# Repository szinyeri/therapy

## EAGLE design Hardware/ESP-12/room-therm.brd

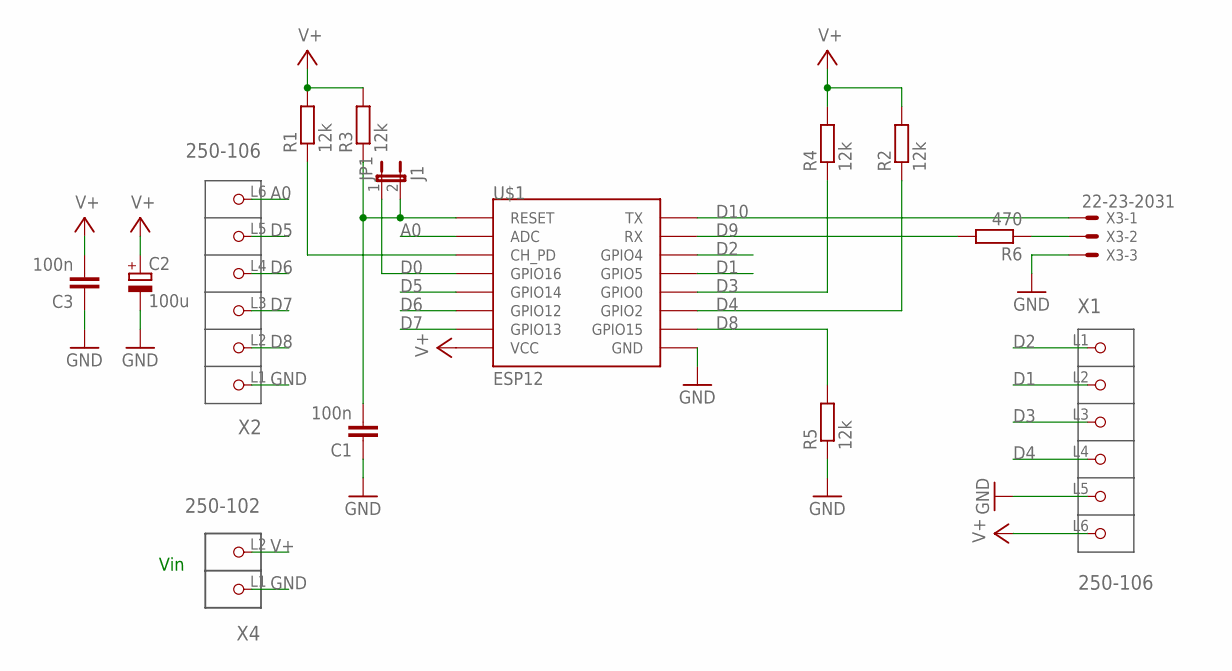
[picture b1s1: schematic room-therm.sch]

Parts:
C1, C3: 100n; C1005
C2: 100u; E2-4
JP1: J1; JP1
R1, R2, R3, R4, R5: 12k; R0805
R6: 470; R0805
U$1: ESP12
X1, X2: 250-106; P-250-106
X3: 22-23-2031
X4: 250-102; P-250-102

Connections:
A0: U$1.ADC, X2.L6 (P6)
D0: JP1.1, U$1.GPIO16
D1: U$1.GPIO5, X1.L2 (P2)
D2: U$1.GPIO4, X1.L1 (P1)
D3: R4.1, U$1.GPIO0, X1.L3 (P3)
D4: R2.1, U$1.GPIO2, X1.L4 (P4)
D5: U$1.GPIO14, X2.L5 (P5)
D6: U$1.GPIO12, X2.L4 (P4)
D7: U$1.GPIO13, X2.L3 (P3)
D8: R5.2, U$1.GPIO15, X2.L2 (P2)
D9: R6.2, U$1.RX
D10: U$1.TX, X3.1
GND: C1.1, C2.-, C3.1, R5.1, U$1.GND, X1.L5 (P5), X2.L1 (P1), X3.3, X4.L1 (P1)
unnamed: C1.2, JP1.2, R3.1, U$1.RESET
unnamed: R1.1, U$1.CH_PD
unnamed: R6.1, X3.2
V+: C2.+, C3.2, R1.2, R2.2, R3.2, R4.2, U$1.VCC, X1.L6 (P6), X4.L2 (P2)

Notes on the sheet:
Vin

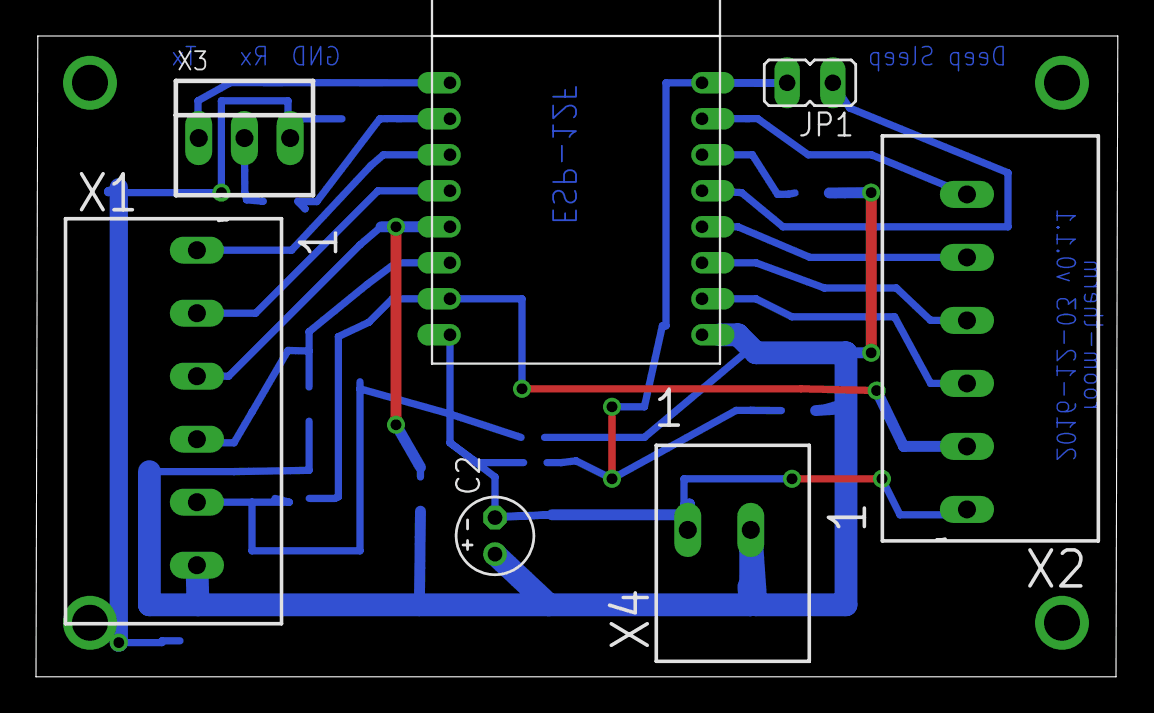
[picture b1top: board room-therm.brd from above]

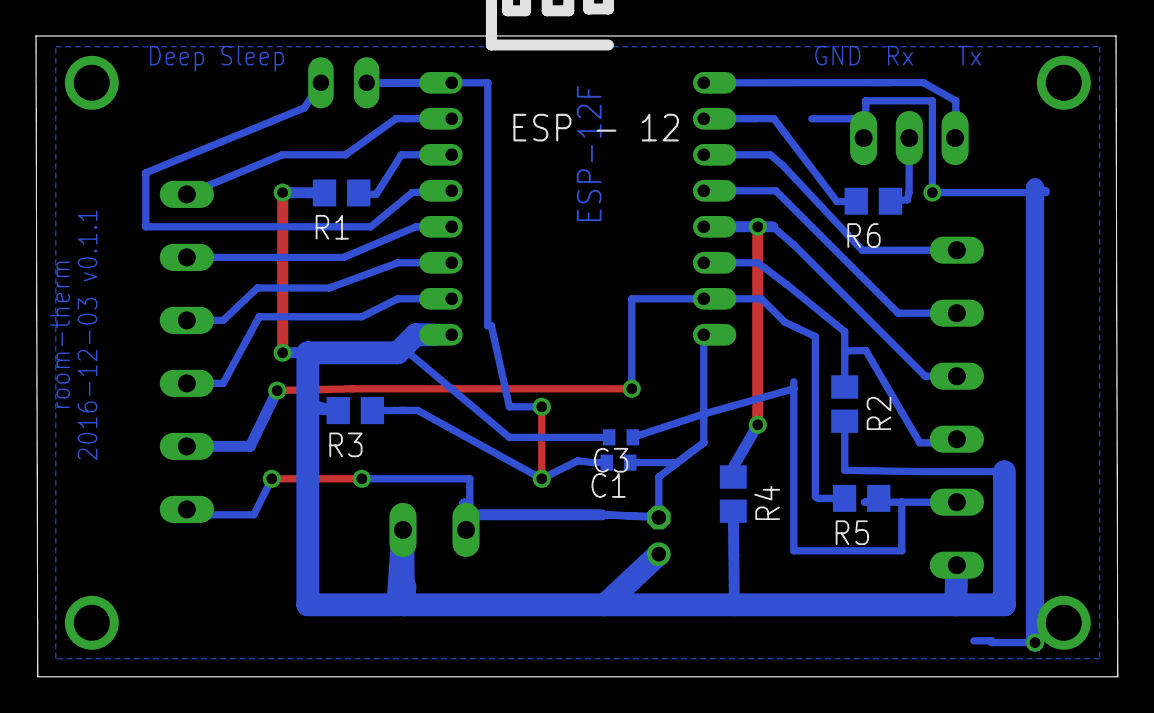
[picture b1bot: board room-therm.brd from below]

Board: 2 copper layers, 60.1 x 35.6 mm, 15 parts (9 on the bottom side), 17 nets.
